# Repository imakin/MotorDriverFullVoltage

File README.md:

# MotorDriverFullVoltage
Brush Motor Driver, with attempt to reduce the voltage drop into minimum. Using MOSFET for speed and relay for direction.

check the jpg/png images.
`Untitled` folder is containing the KiCad projects (schematic, boards)

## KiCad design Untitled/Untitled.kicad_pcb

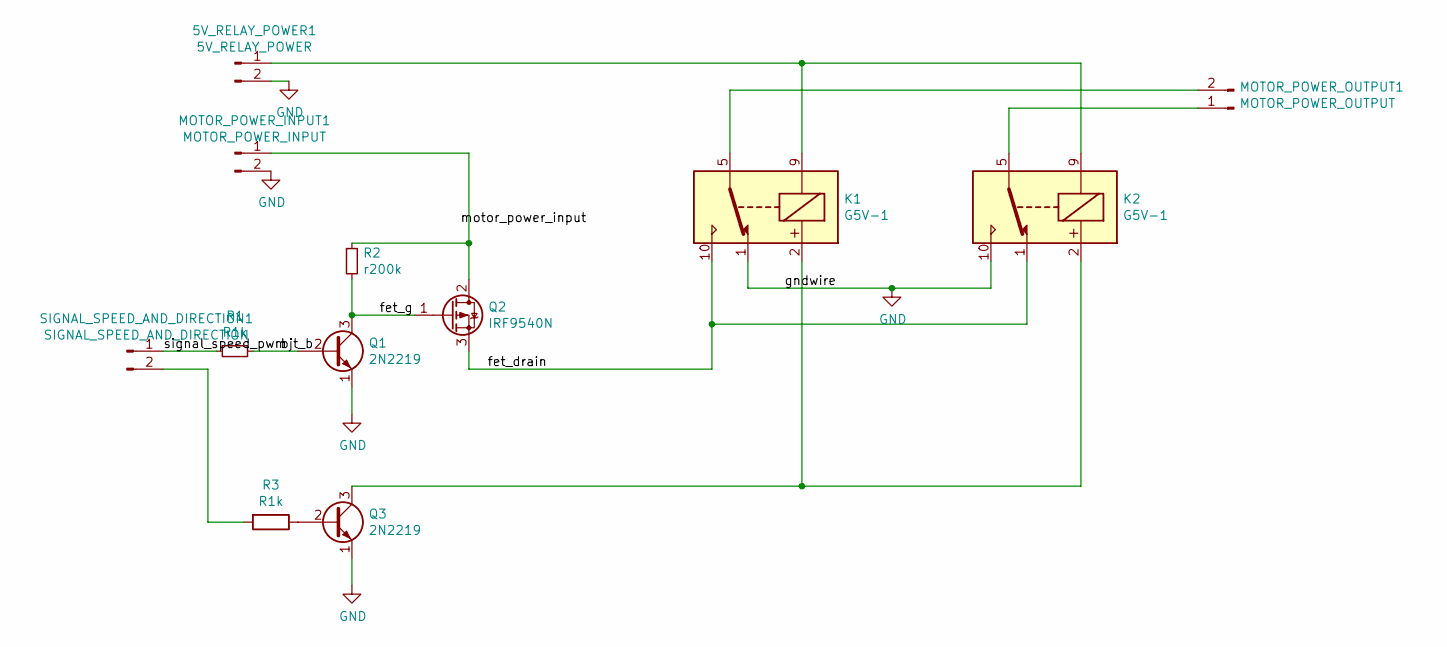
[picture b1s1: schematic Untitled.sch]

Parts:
5V_RELAY_POWER1: 5V_RELAY_POWER; PinHeader_1x02_P2.54mm_Vertical
K1, K2: G5V-1; Relay_SPDT_Omron_G5V-1
MOTOR_POWER_INPUT1: MOTOR_POWER_INPUT; PinHeader_1x02_P2.54mm_Vertical
MOTOR_POWER_OUTPUT1: MOTOR_POWER_OUTPUT; PinHeader_1x02_P2.54mm_Vertical
Q1, Q3: 2N2219; TO-92L_Inline_Wide
Q2: IRF9540N; TO-220-3_Vertical
R1, R3: R1k; R_Axial_DIN0207_L6.3mm_D2.5mm_P10.16mm_Horizontal
R2: r200k; R_Axial_DIN0207_L6.3mm_D2.5mm_P10.16mm_Horizontal
SIGNAL_SPEED_AND_DIRECTION1: SIGNAL_SPEED_AND_DIRECTION; PinHeader_1x02_P2.54mm_Vertical

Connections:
/bjt_b: Q1.2 (B), R1.1
/fet_drain: K1.10, K2.1, Q2.3 (S)
/fet_g: Q1.3 (C), Q2.1 (G), R2.2
/signal_speed_pwm: R1.2, SIGNAL_SPEED_AND_DIRECTION1.1
GND: 5V_RELAY_POWER1.2, K1.1, K2.10, MOTOR_POWER_INPUT1.2, Q1.1 (E), Q3.1 (E)
unnamed: 5V_RELAY_POWER1.1, K1.9, K2.9
unnamed: K1.2, K2.2, Q3.3 (C)
unnamed: K1.5, K1.6, MOTOR_POWER_OUTPUT1.2
unnamed: K2.5, K2.6, MOTOR_POWER_OUTPUT1.1
unnamed: MOTOR_POWER_INPUT1.1, Q2.2 (D), R2.1
unnamed: Q3.2 (B), R3.1
unnamed: R3.2, SIGNAL_SPEED_AND_DIRECTION1.2

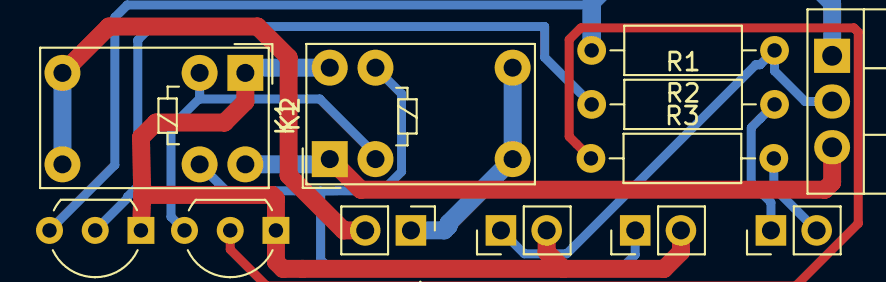
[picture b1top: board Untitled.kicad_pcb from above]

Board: 2 copper layers, 12 parts (0 on the bottom side), 12 nets.

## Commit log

2020-04-12 Add files
